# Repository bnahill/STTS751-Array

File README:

Array of STTS751 temperature sensors to connect to STM32F4-Discovery board

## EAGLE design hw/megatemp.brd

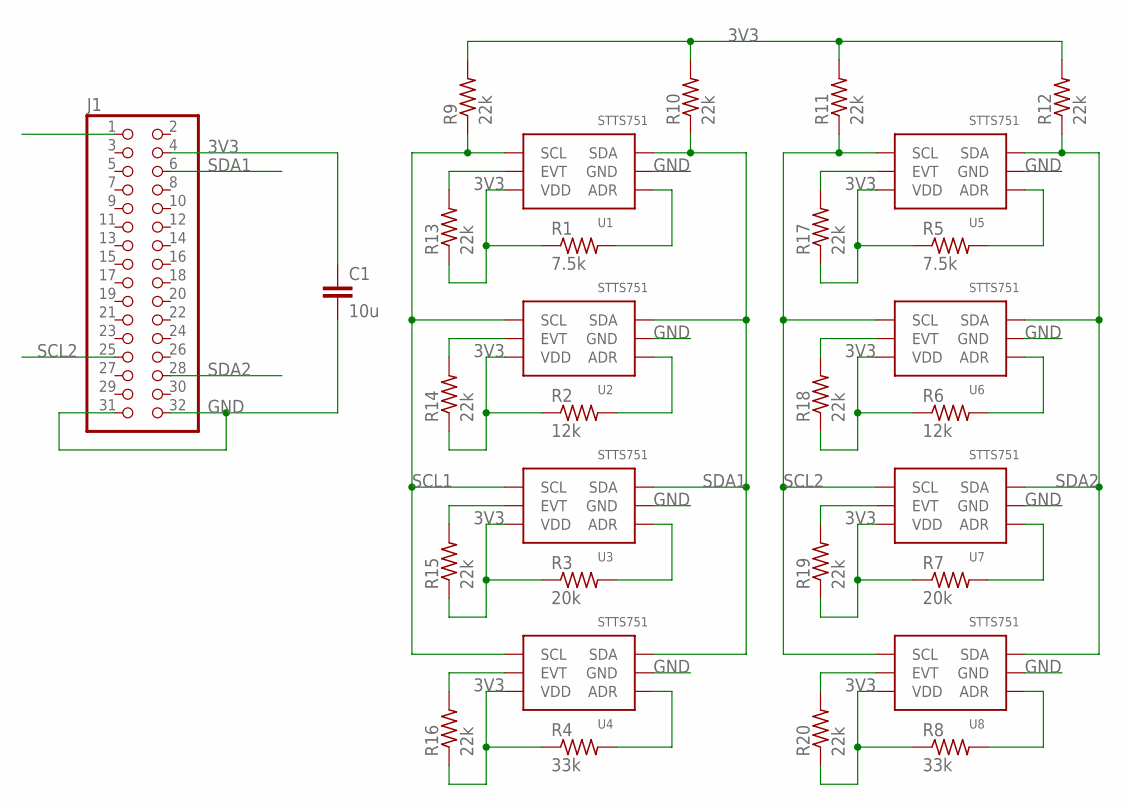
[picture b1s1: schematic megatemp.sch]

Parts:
C1: 10u; C0805
J1: PINHD-2X16; 2X16
R1, R5: 7.5k; R0402
R2, R6: 12k; R0402
R3, R7: 20k; R0402
R4, R8: 33k; R0402
R9, R10, R11, R12, R13, R14, R15, R16, R17, R18, R19, R20: 22k; R0402
U1, U2, U3, U4, U5, U6, U7, U8: STTS751; ST_UDFN-6L_2X2

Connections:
3V3: C1.1, J1.4, R1.1, R2.1, R3.1, R4.1, R5.1, R6.1, R7.1, R8.1, R9.2, R10.2, R11.2, R12.2, R13.1, R14.1, R15.1, R16.1, R17.1, R18.1, R19.1, R20.1, U1.3 (VDD), U2.3 (VDD), U3.3 (VDD), U4.3 (VDD), U5.3 (VDD), U6.3 (VDD), U7.3 (VDD), U8.3 (VDD)
GND: C1.2, J1.31, J1.32, U1.5 (GND), U2.5 (GND), U3.5 (GND), U4.5 (GND), U5.5 (GND), U6.5 (GND), U7.5 (GND), U8.5 (GND)
unnamed: R13.2, U1.2 (EVT)
unnamed: R1.2, U1.4 (ADR)
unnamed: R2.2, U2.4 (ADR)
unnamed: R20.2, U8.2 (EVT)
unnamed: R3.2, U3.4 (ADR)
unnamed: R14.2, U2.2 (EVT)
unnamed: R4.2, U4.4 (ADR)
unnamed: R15.2, U3.2 (EVT)
unnamed: R8.2, U8.4 (ADR)
unnamed: R16.2, U4.2 (EVT)
unnamed: R7.2, U7.4 (ADR)
unnamed: R6.2, U6.4 (ADR)
unnamed: R19.2, U7.2 (EVT)
unnamed: R5.2, U5.4 (ADR)
unnamed: R18.2, U6.2 (EVT)
unnamed: R17.2, U5.2 (EVT)
SCL1: J1.1, R9.1, U1.1 (SCL), U2.1 (SCL), U3.1 (SCL), U4.1 (SCL)
SCL2: J1.25, R11.1, U5.1 (SCL), U6.1 (SCL), U7.1 (SCL), U8.1 (SCL)
SDA1: J1.6, R10.1, U1.6 (SDA), U2.6 (SDA), U3.6 (SDA), U4.6 (SDA)
SDA2: J1.28, R12.1, U5.6 (SDA), U6.6 (SDA), U7.6 (SDA), U8.6 (SDA)

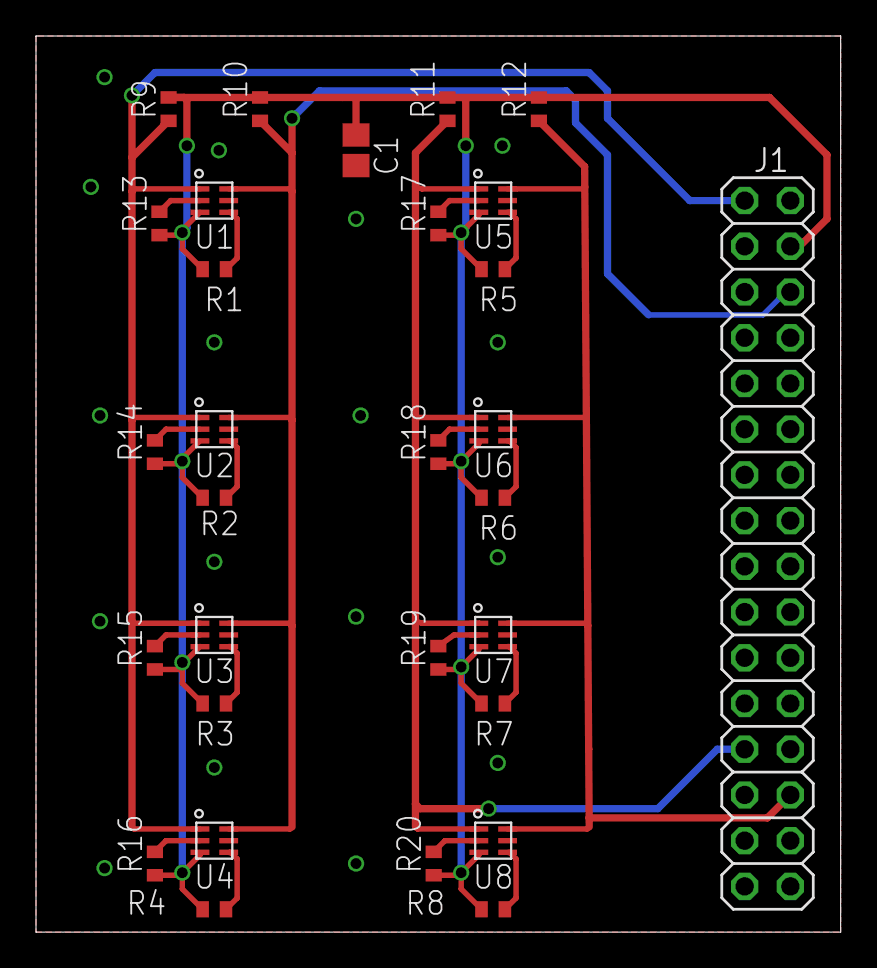
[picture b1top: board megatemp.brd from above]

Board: 2 copper layers, 44.7 x 49.8 mm, 30 parts (0 on the bottom side), 22 nets.

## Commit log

2012-03-13 Initial commit of design
2012-03-13 Added README
2012-03-16 Changed a name
2012-03-19 Generated gerbers
2012-03-30 Software added
2012-03-30 Updated design to a functional schematic
2012-03-30 Documentation for new C++ stuffs, got rid of clock out config
2012-03-31 Added Doxygen support
2012-03-31 Restructured to avoid requirement for immediate constructor calls, now tested with all 4 sensors
2012-04-02 Fixed timer
2012-04-03 Experimenting with linker script to get static constructors
2012-04-03 Added missing source files
2012-04-03 Added python script to read data dumped from flash
2012-04-03 Separated out the ticker
2012-04-03 Fixed bug in flash, everything seems to work now
2012-04-03 Fixed flash not erasing everything
2012-04-03 Fixed Python script messing up the data
2012-04-04 Actually fixed flash this time...
2012-04-04 Added some bounds checking for flash operations
2012-04-04 Added a parameter to the tick mechanism
2012-04-05 Tested flash to ensure it can write some 128k samples
2012-04-05 Data extraction tool now outputs matlab too
2012-04-06 Converted everything to C - Has yet to be tested on the board or in Keil
2012-04-06 Made working Keil project. GNU-based project still seems to work but won't be merged back until this is verified.
2012-04-06 New startup for GNU toolchain since FPU config is now handled elsewhere
